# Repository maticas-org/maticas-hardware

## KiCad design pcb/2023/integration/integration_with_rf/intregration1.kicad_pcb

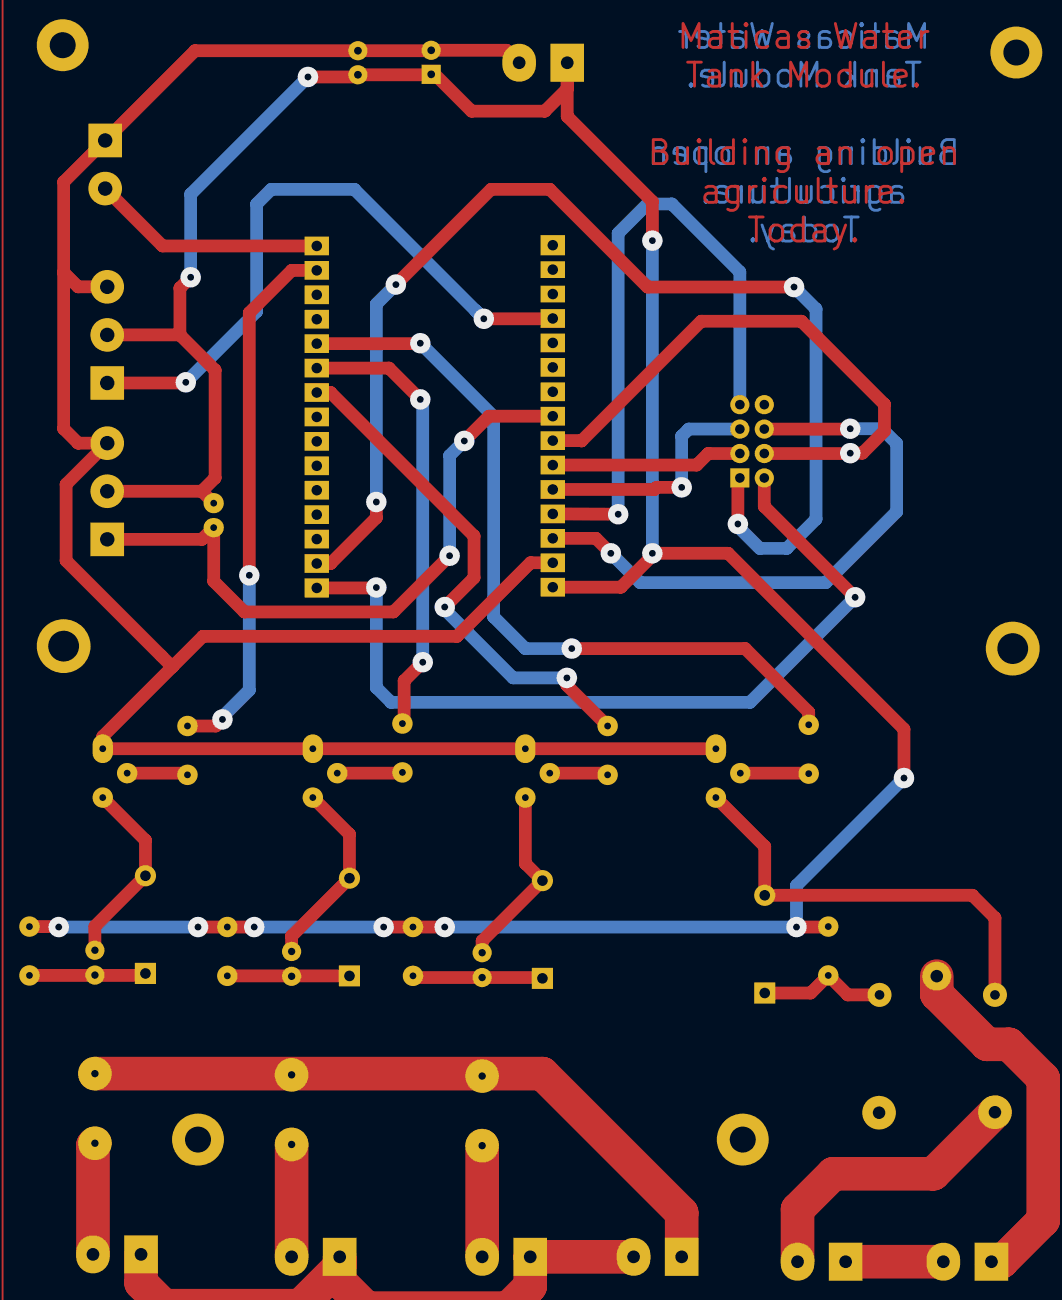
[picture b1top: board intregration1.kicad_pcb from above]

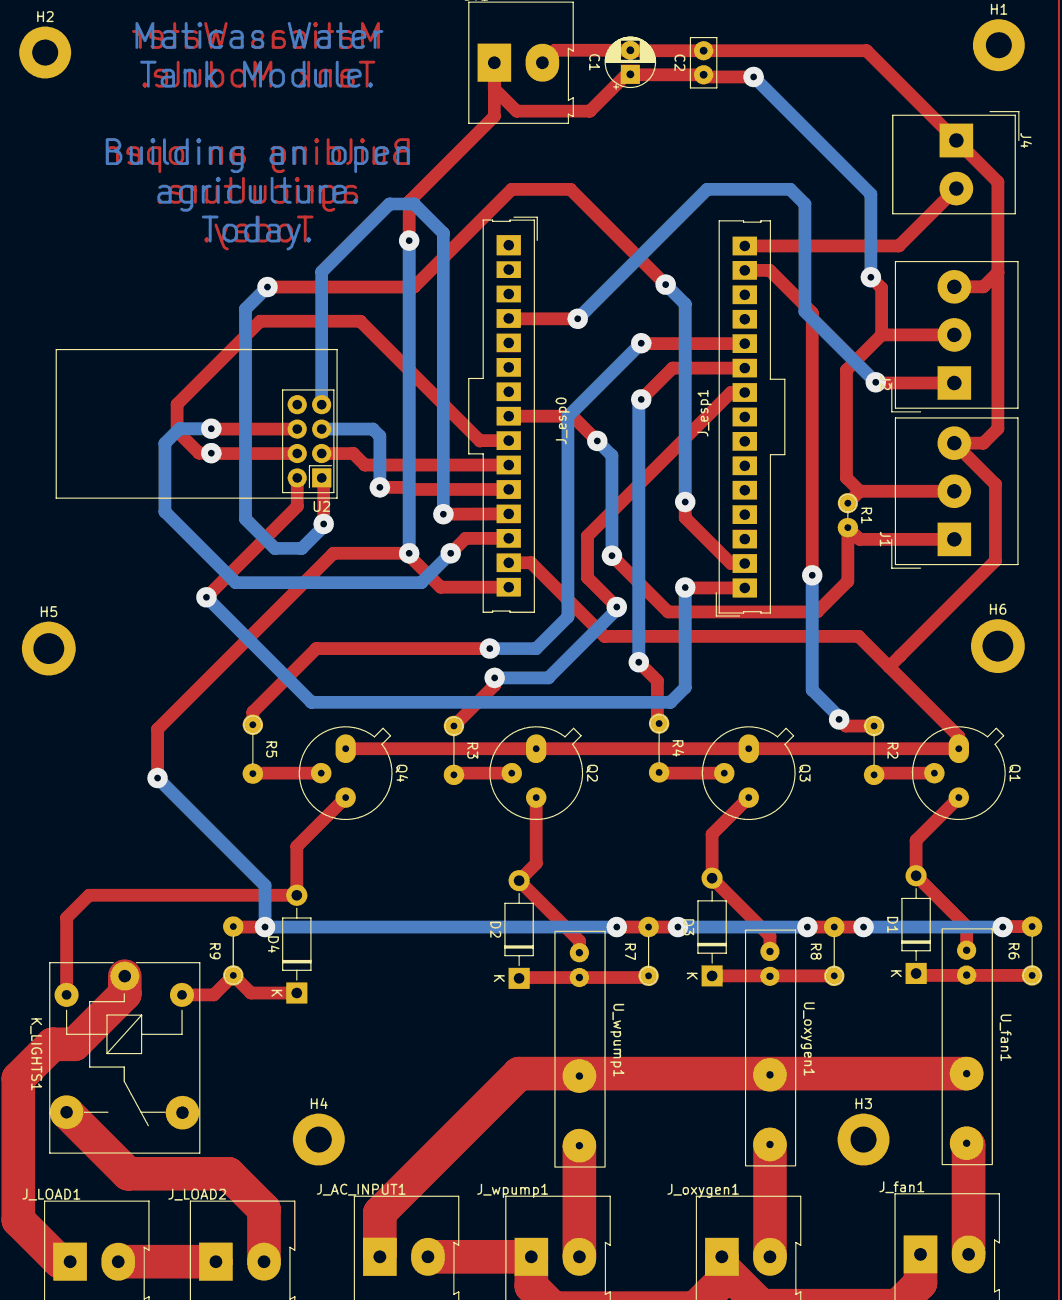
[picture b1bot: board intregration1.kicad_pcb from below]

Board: 2 copper layers, 42 parts (42 on the bottom side), 36 nets.

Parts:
5V1: Screw_Terminal_01x02; TerminalBlock_Altech_AK300-2_P5.00mm
C1: C_Polarized; CP_Radial_D5.0mm_P2.50mm
C2: C_Generic; C_Disc_D5.0mm_W2.5mm_P2.50mm
D1, D2, D3, D4: 1N4004; D_DO-41_SOD81_P10.16mm_Horizontal
H1, H2, H3, H4: MountingHole; MountingHole_2.7mm_M2.5_Pad
H5, H6: MountingHole; MountingHole_3.2mm_M3_DIN965_Pad
J1, J2: Screw_Terminal_01x03; Altech_AK300_1x03_P5.00mm_45-Degree
J4: Screw_Terminal_01x02; Altech_AK300_1x02_P5.00mm_45-Degree
J_AC_INPUT1: Screw_Terminal_01x02; TerminalBlock_Altech_AK300-2_P5.00mm
J_LOAD1, J_LOAD2: Screw_Terminal_01x02; TerminalBlock_Altech_AK300-2_P5.00mm
J_esp0, J_esp1: Conn_01x15_Female; Connector_Molex_Molex_SL_171971-0015_1x15_P2.54mm_Vertical_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
J_fan1: Screw_Terminal_01x02; TerminalBlock_Altech_AK300-2_P5.00mm
J_oxygen1: Screw_Terminal_01x02; TerminalBlock_Altech_AK300-2_P5.00mm
J_wpump1: Screw_Terminal_01x02; TerminalBlock_Altech_AK300-2_P5.00mm
K_LIGHTS1: SANYOU_SRD_Form_C; Relay_SPDT_SANYOU_SRD_Series_Form_C
Q1, Q2, Q3, Q4: 2N2219; TO-39-3
R1: 4.7k; R_Axial_DIN0204_L3.6mm_D1.6mm_P2.54mm_Vertical
R2, R3, R4, R5: 660; R_Axial_DIN0204_L3.6mm_D1.6mm_P5.08mm_Vertical
R6, R7, R8, R9: R; R_Axial_DIN0204_L3.6mm_D1.6mm_P5.08mm_Vertical
U2: NRF24L01_Breakout; nRF24L01_Breakout
U_fan1: 34.81-8240; G3MB-202P
U_oxygen1: 34.81-8240; G3MB-202P
U_wpump1: 34.81-8240; G3MB-202P

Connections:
3V3: J_esp1.1, U2.2 (VCC)
5v: 5V1.1, C1.1, C2.1, J1.2, J2.2, J_esp0.15, R1.1, R6.2, R7.2, R8.2, R9.2
AC1: J_AC_INPUT1.1, U_fan1.11, U_oxygen1.11, U_wpump1.11
AC2: J_AC_INPUT1.2, J_fan1.1, J_oxygen1.1, J_wpump1.1
D12: J_esp0.12, U2.7 (MISO)
D13: J_esp0.13, U2.6 (MOSI)
D14: J_esp0.11, U2.5 (SCK)
D18: J_esp1.9, R3.1
D19: J_esp1.10, R4.1
D21: J_esp1.11, R5.1
D22: J_esp1.14, R2.1
D23: J4.2, J_esp1.15
D25: J1.1, J_esp0.8, R1.2
D26: J_esp0.9, U2.4 (~CSN)
D27: J_esp0.10, U2.3 (CE)
D34: J2.1, J_esp0.4
GND2: J_esp1.2, U2.1 (GND)
GND5V: 5V1.2, C1.2, C2.2, J1.3, J2.3, J4.1, J_esp0.14, Q1.1 (E), Q2.1 (E), Q3.1 (E), Q4.1 (E)
GND LOAD: J_LOAD1.2, J_LOAD2.1
LOAD IN: J_LOAD1.1, K_LIGHTS1.1
unnamed: D1.2 (A), Q1.3 (C), U_fan1.A2
unnamed: D1.1 (K), R6.1, U_fan1.A1
unnamed: D2.2 (A), Q2.3 (C), U_wpump1.A2
unnamed: D2.1 (K), R7.1, U_wpump1.A1
unnamed: D3.2 (A), Q3.3 (C), U_oxygen1.A2
unnamed: D3.1 (K), R8.1, U_oxygen1.A1
unnamed: D4.2 (A), K_LIGHTS1.2, Q4.3 (C)
unnamed: D4.1 (K), K_LIGHTS1.5, R9.1
unnamed: J_fan1.2, U_fan1.14
unnamed: J_oxygen1.2, U_oxygen1.14
unnamed: J_wpump1.2, U_wpump1.14
unnamed: Q1.2 (B), R2.2
unnamed: Q2.2 (B), R3.2
unnamed: Q3.2 (B), R4.2
unnamed: Q4.2 (B), R5.2
Normally O: J_LOAD2.2, K_LIGHTS1.3

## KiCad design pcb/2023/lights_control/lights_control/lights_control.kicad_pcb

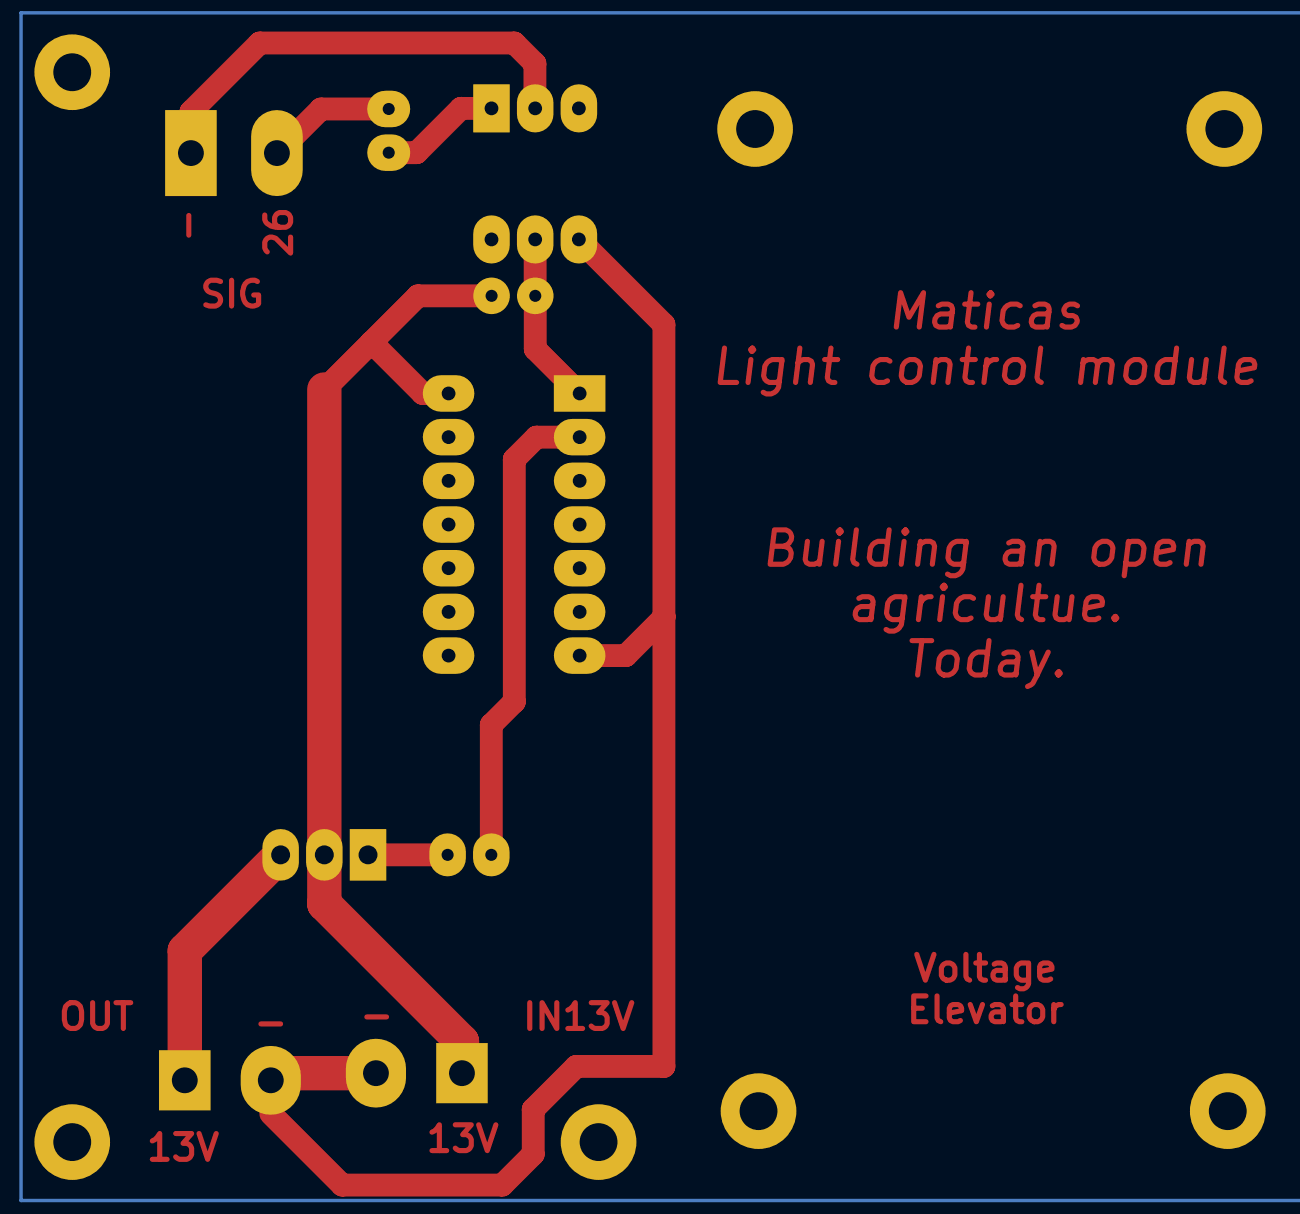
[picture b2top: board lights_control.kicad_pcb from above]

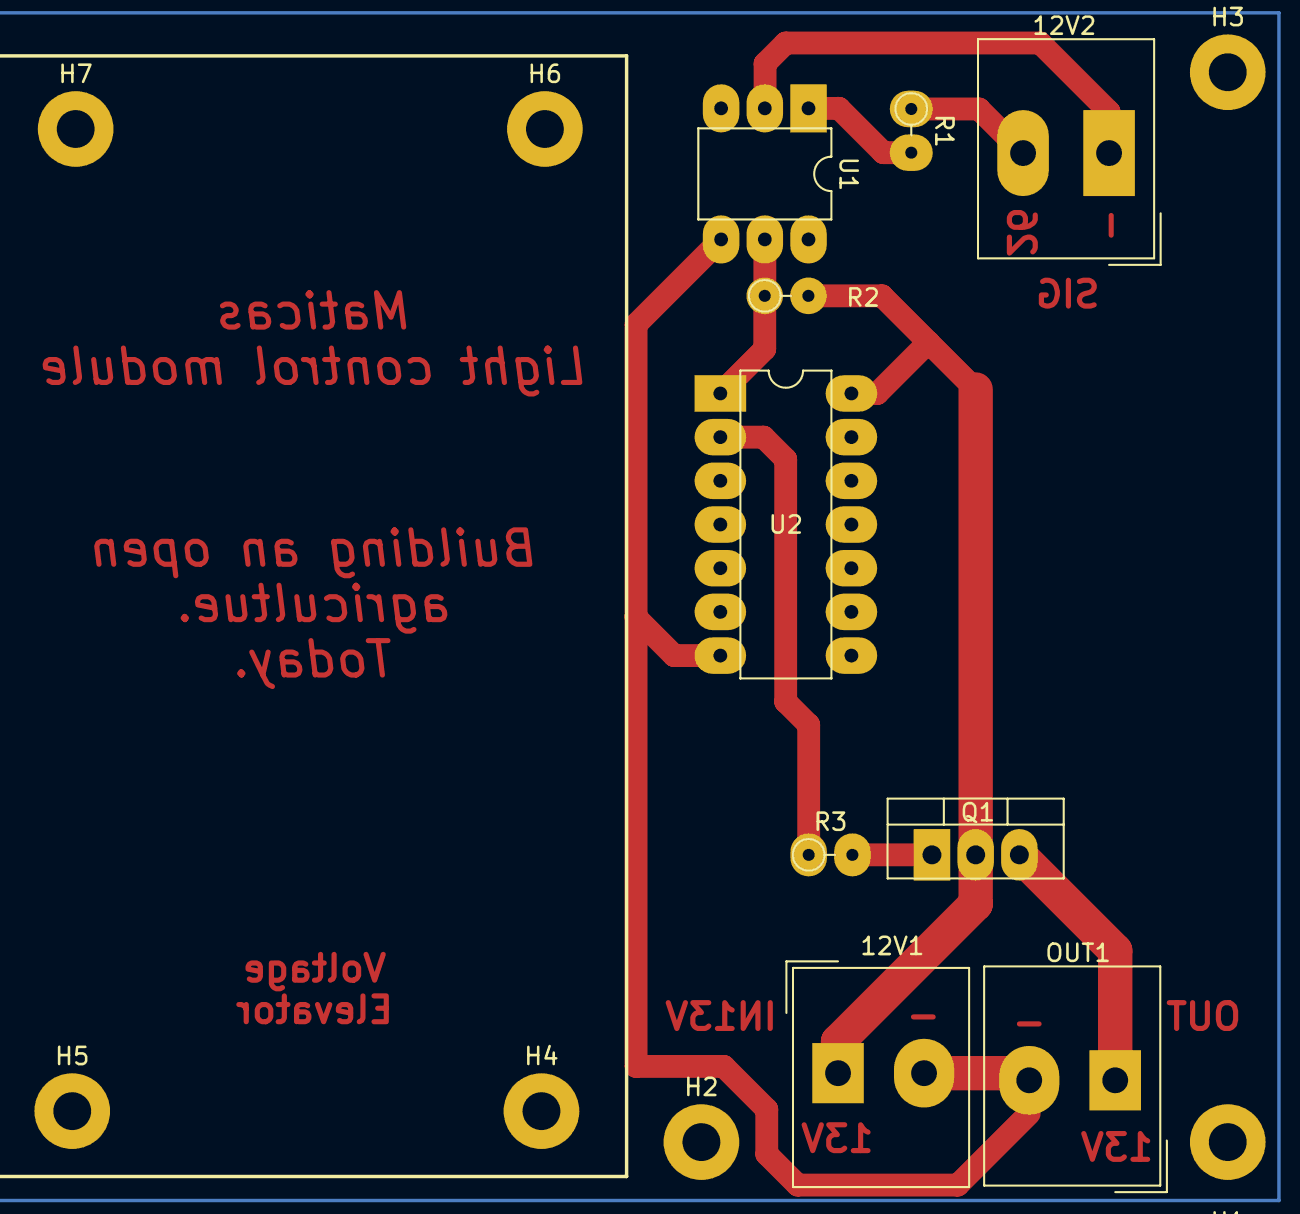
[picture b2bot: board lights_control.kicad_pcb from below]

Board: 2 copper layers, 16 parts (16 on the bottom side), 9 nets.

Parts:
12V1, 12V2: Screw_Terminal_01x02; Altech_AK300_1x02_P5.00mm_45-Degree
H1, H2, H3, H4, H5, H6, H7: MountingHole; MountingHole_2.2mm_M2_Pad
OUT1: Screw_Terminal_01x02; Altech_AK300_1x02_P5.00mm_45-Degree
Q1: TIP122; TO-220-3_Vertical
R1: 100; R_Axial_DIN0204_L3.6mm_D1.6mm_P2.54mm_Vertical
R2: 10k; R_Axial_DIN0204_L3.6mm_D1.6mm_P2.54mm_Vertical
R3: 10; R_Axial_DIN0204_L3.6mm_D1.6mm_P2.54mm_Vertical
U1: 4N25; DIP-6_W7.62mm
U2: 40106; DIP-14_W7.62mm

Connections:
12v: 12V1.1, Q1.2 (C), R2.2, U2.14 (VDD)
D26: 12V2.2, R1.1
GND12V: 12V1.2, OUT1.2, U1.4, U2.7 (VSS)
GND SIG: 12V2.1, U1.2
unnamed: OUT1.1, Q1.3 (E)
unnamed: Q1.1 (B), R3.2
unnamed: R1.2, U1.1
unnamed: R2.1, U1.5, U2.1
unnamed: R3.1, U2.2

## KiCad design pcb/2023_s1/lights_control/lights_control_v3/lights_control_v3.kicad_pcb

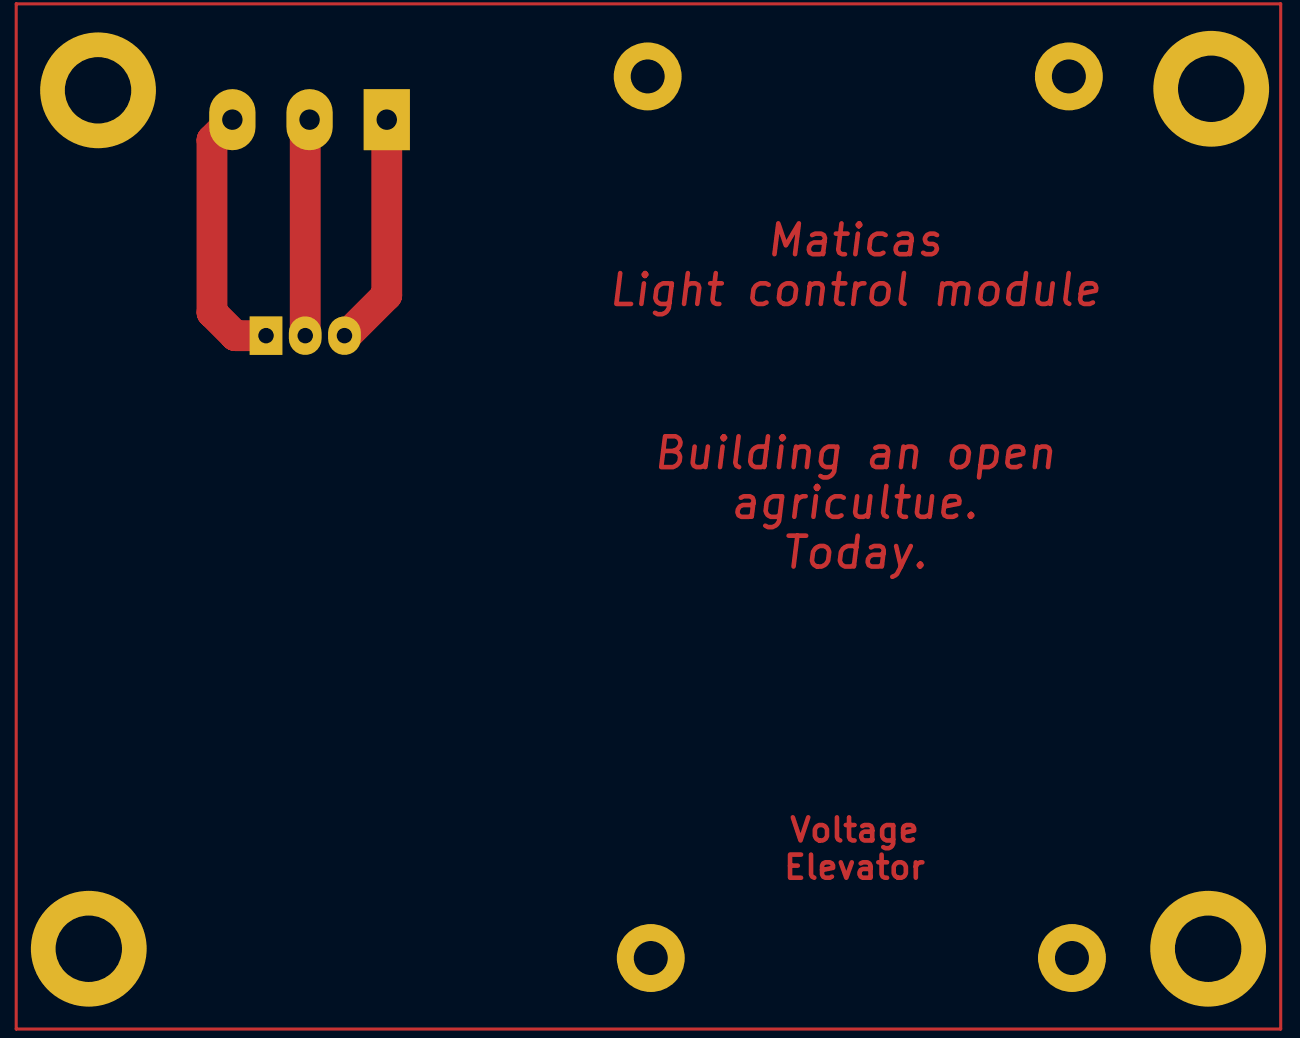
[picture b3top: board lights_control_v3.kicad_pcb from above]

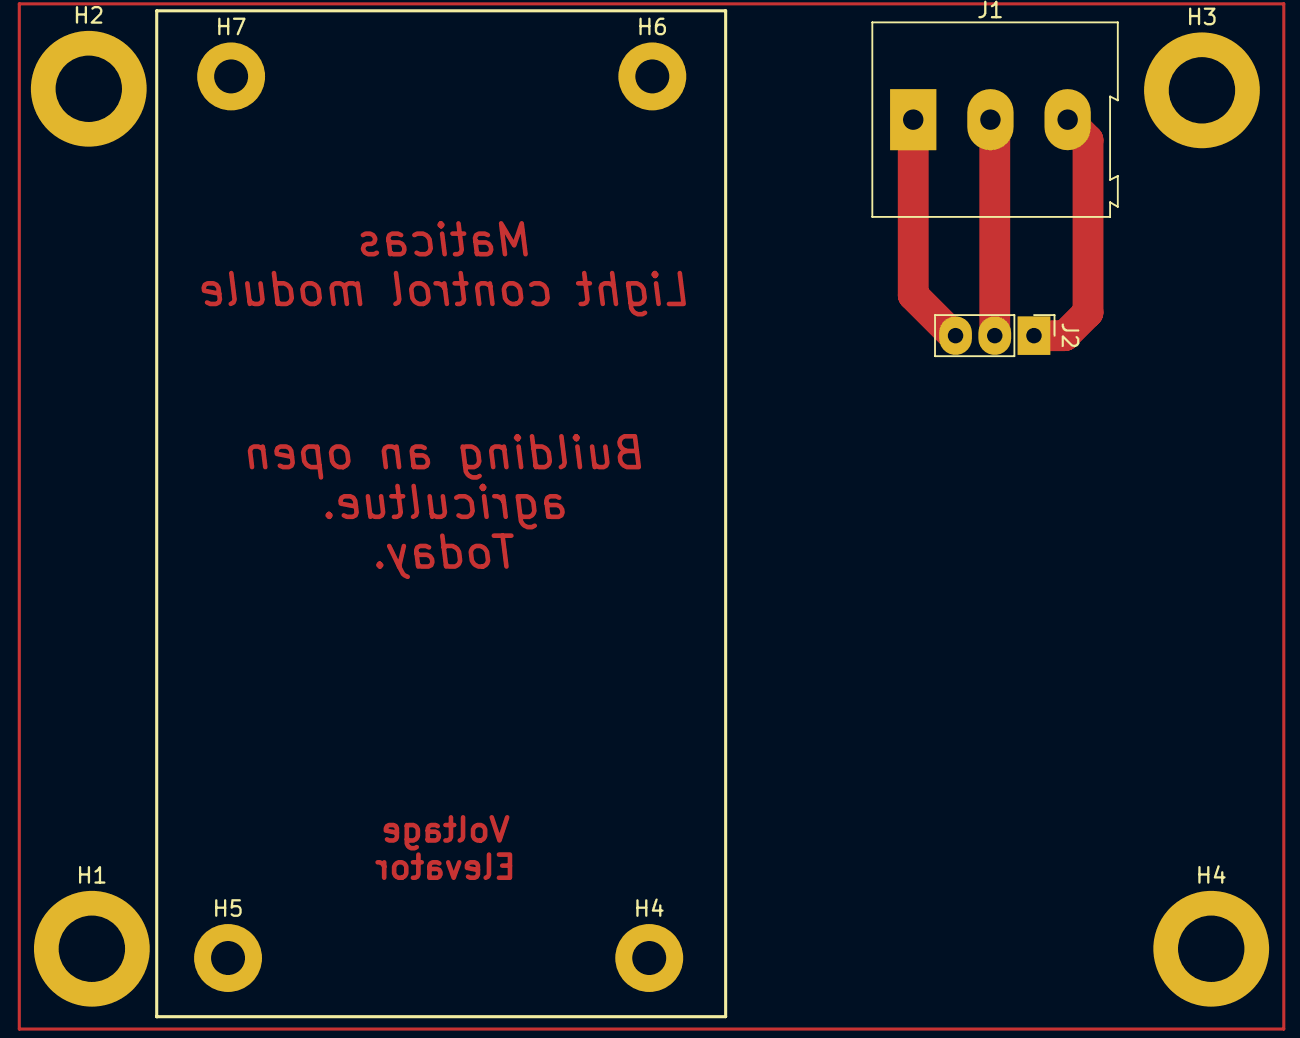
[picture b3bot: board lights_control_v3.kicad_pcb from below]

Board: 2 copper layers, 10 parts (10 on the bottom side), 3 nets.

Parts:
H1, H2, H3, H4: MountingHole; MountingHole_4.3mm_M4_DIN965_Pad
H4#2, H5, H6, H7: MountingHole; MountingHole_2.2mm_M2_Pad
J1: Screw_Terminal_01x03; TerminalBlock_Altech_AK300-3_P5.00mm
J2: Conn_01x03_Male; PinHeader_1x03_P2.54mm_Vertical

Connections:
3.3V SIG: J1.3, J2.1
5V+: J1.2, J2.2
GND5V: J1.1, J2.3

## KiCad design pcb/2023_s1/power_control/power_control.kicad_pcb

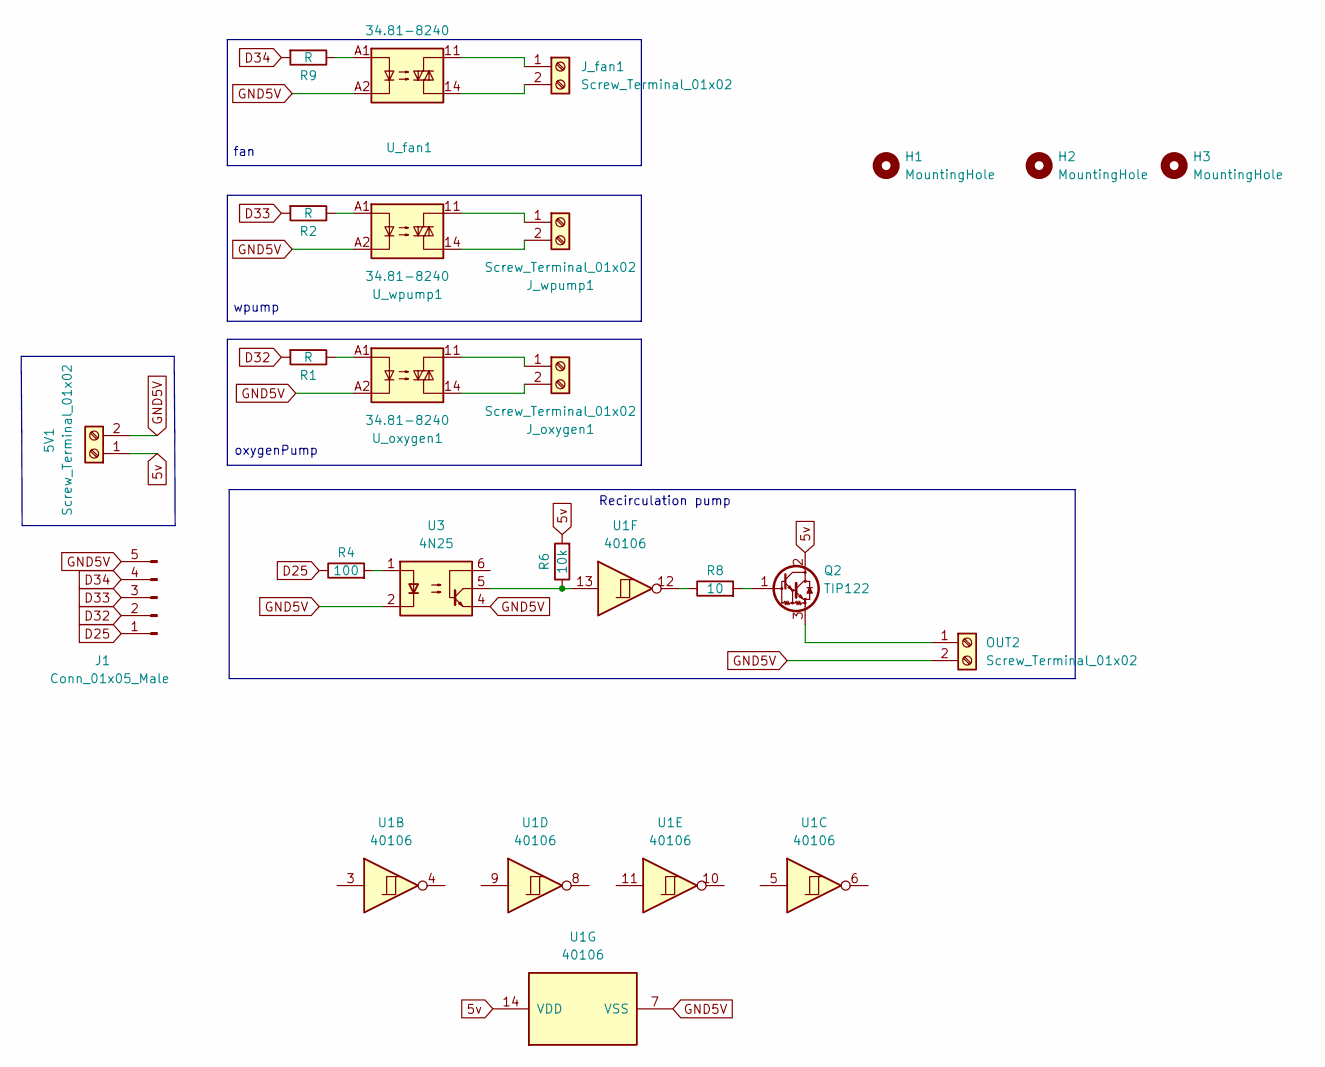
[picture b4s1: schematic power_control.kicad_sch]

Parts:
5V1: Screw_Terminal_01x02; TerminalBlock_Altech_AK300-2_P5.00mm
H1, H2, H3: MountingHole; MountingHole_3.2mm_M3_DIN965_Pad
J1: Conn_01x05_Male; JST_EH_B5B-EH-A_1x05_P2.50mm_Vertical
J_fan1: Screw_Terminal_01x02; TerminalBlock_Altech_AK300-2_P5.00mm
J_oxygen1: Screw_Terminal_01x02; TerminalBlock_Altech_AK300-2_P5.00mm
J_wpump1: Screw_Terminal_01x02; TerminalBlock_Altech_AK300-2_P5.00mm
OUT2: Screw_Terminal_01x02; TerminalBlock_Altech_AK300-2_P5.00mm
Q2: TIP122; TO-220-3_Vertical
R1, R2, R9: R; R_Axial_DIN0204_L3.6mm_D1.6mm_P5.08mm_Vertical
R4: 100; R_Axial_DIN0204_L3.6mm_D1.6mm_P2.54mm_Vertical
R6: 10k; R_Axial_DIN0204_L3.6mm_D1.6mm_P2.54mm_Vertical
R8: 10; R_Axial_DIN0204_L3.6mm_D1.6mm_P2.54mm_Vertical
U1: 40106; DIP-14_W7.62mm
U3: 4N25; DIP-6_W7.62mm
U_fan1: 34.81-8240; Finder_34.81
U_oxygen1: 34.81-8240; Finder_34.81
U_wpump1: 34.81-8240; Finder_34.81

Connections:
5v: 5V1.1, Q2.2 (C), R6.2, U1.14 (VDD)
D25: J1.1, R4.1
D32: J1.2, R1.2
D33: J1.3, R2.2
D34: J1.4, R9.2
GND5V: 5V1.2, J1.5, OUT2.2, U1.7 (VSS), U3.2, U3.4, U_fan1.A2, U_oxygen1.A2, U_wpump1.A2
unnamed: J_fan1.1, U_fan1.11
unnamed: J_fan1.2, U_fan1.14
unnamed: J_oxygen1.1, U_oxygen1.11
unnamed: J_oxygen1.2, U_oxygen1.14
unnamed: J_wpump1.1, U_wpump1.11
unnamed: J_wpump1.2, U_wpump1.14
unnamed: OUT2.1, Q2.3 (E)
unnamed: Q2.1 (B), R8.2
unnamed: R1.1, U_oxygen1.A1
unnamed: R2.1, U_wpump1.A1
unnamed: R4.2, U3.1
unnamed: R6.1, U1.13, U3.5
unnamed: R8.1, U1.12
unnamed: R9.1, U_fan1.A1

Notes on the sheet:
fan
wpump
oxygenPump
Recirculation pump

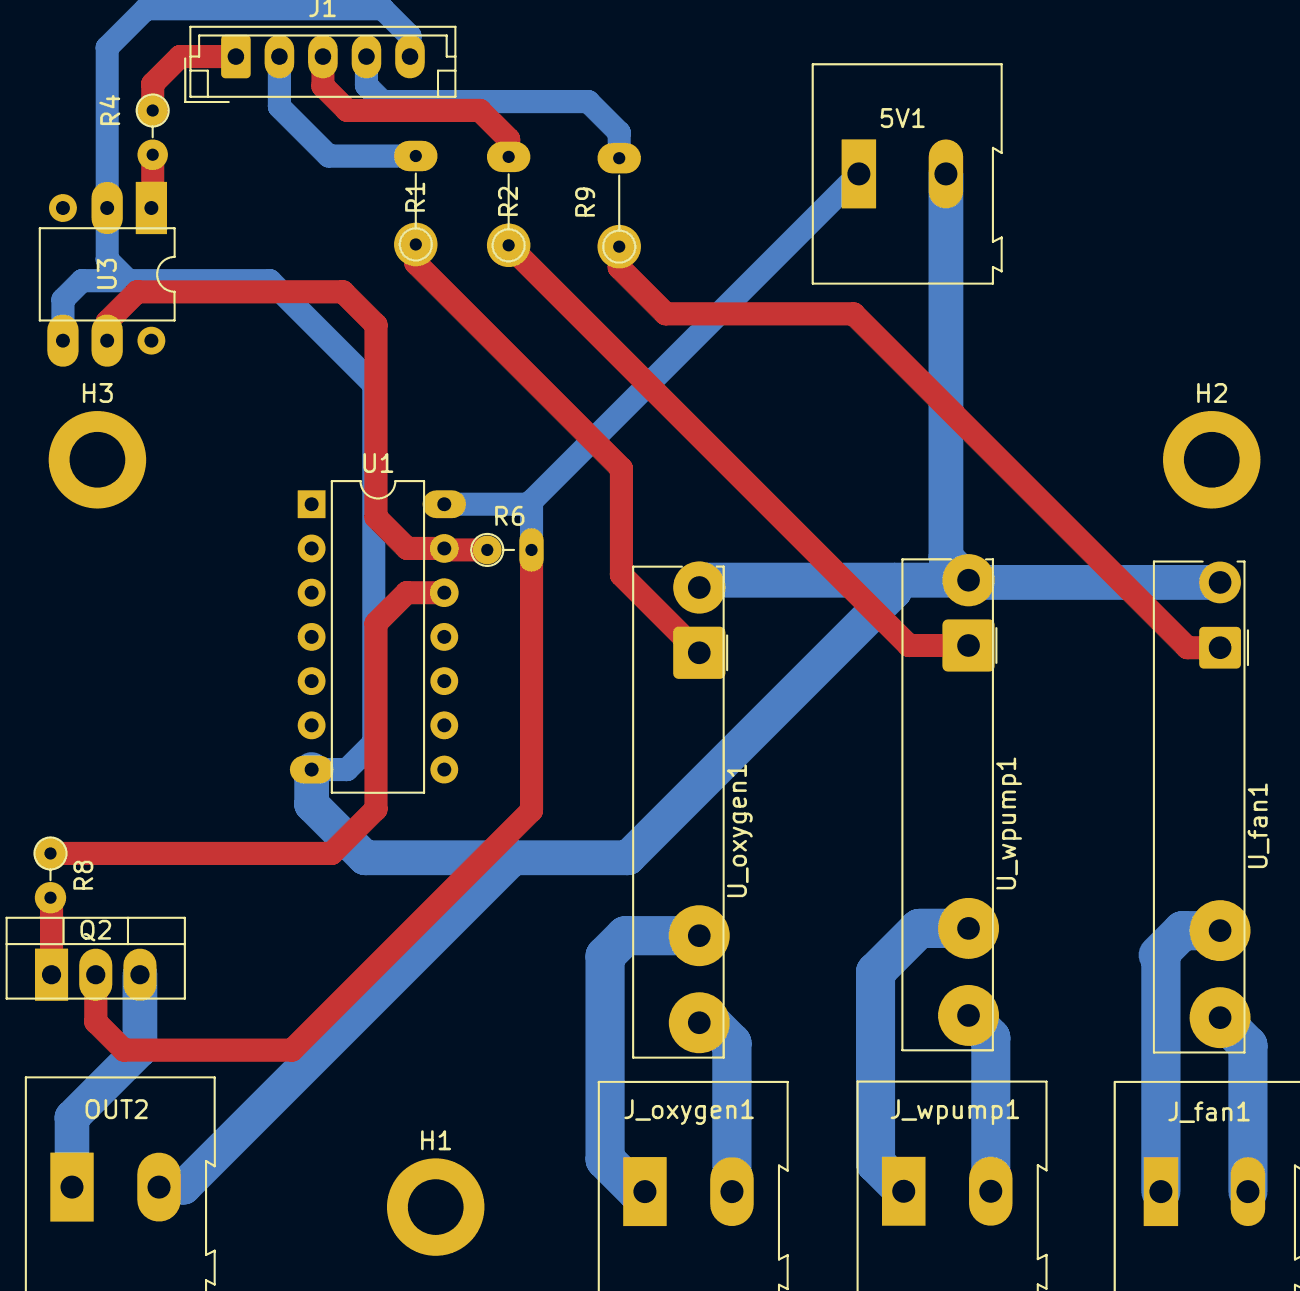
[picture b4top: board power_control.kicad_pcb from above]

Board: 2 copper layers, 21 parts (0 on the bottom side), 20 nets.

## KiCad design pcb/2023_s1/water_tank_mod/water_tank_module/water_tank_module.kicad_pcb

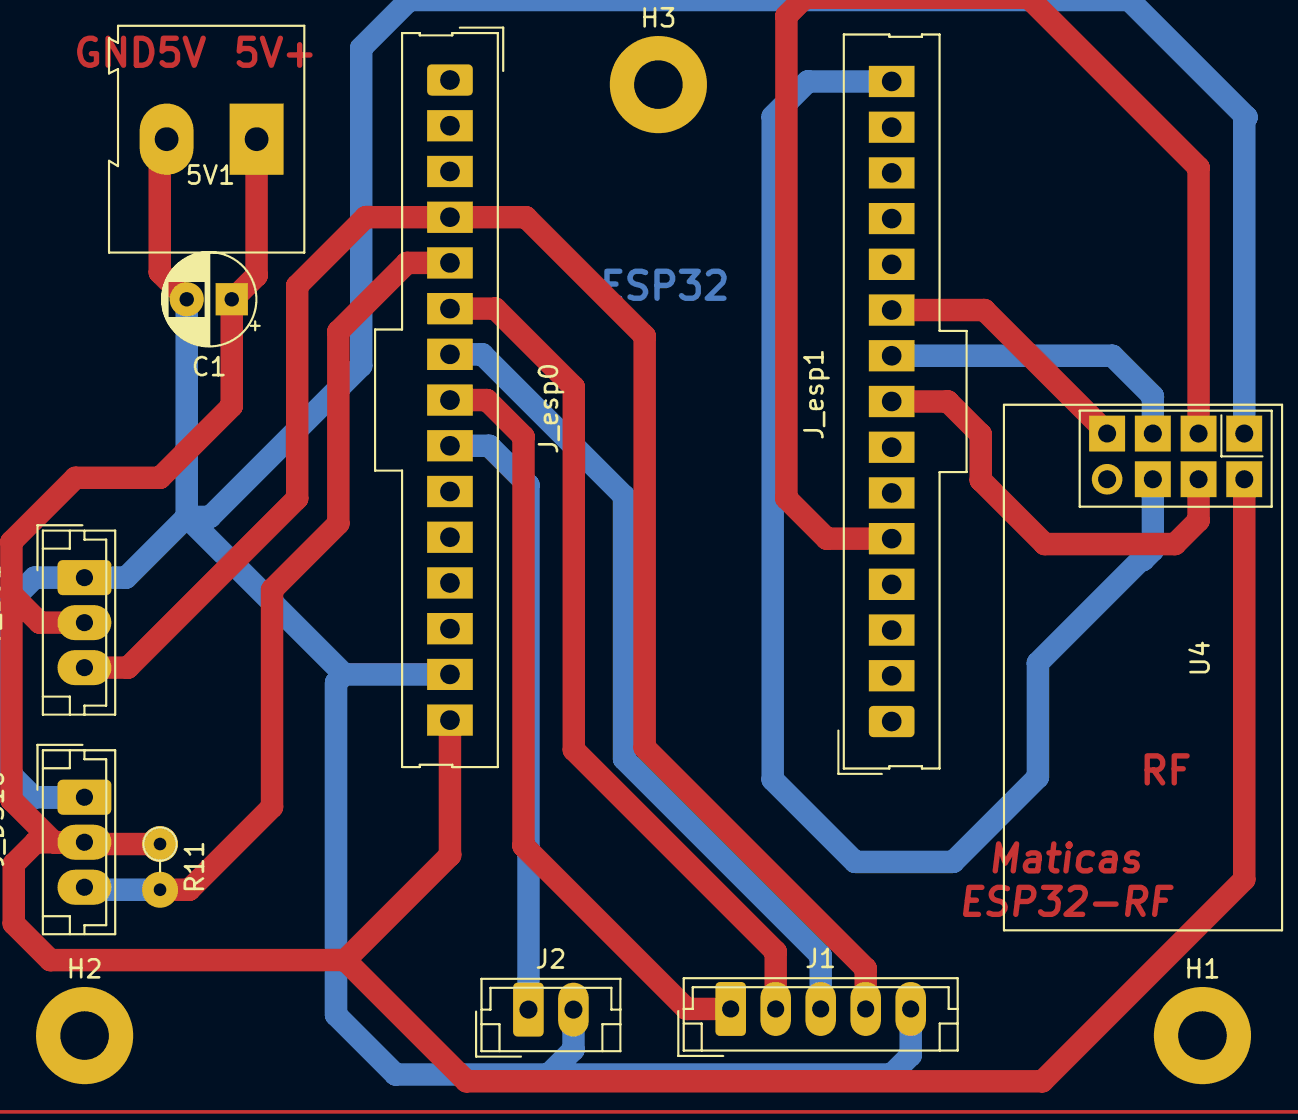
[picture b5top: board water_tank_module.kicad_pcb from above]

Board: 2 copper layers, 13 parts (0 on the bottom side), 13 nets.

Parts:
5V1: Screw_Terminal_01x02; TerminalBlock_Altech_AK300-2_P5.00mm
C1: C_Polarized; CP_Radial_D5.0mm_P2.50mm
H1, H2, H3: MountingHole; MountingHole_2.7mm_M2.5_Pad
J1: Conn_01x05_Male; JST_EH_B5B-EH-A_1x05_P2.50mm_Vertical
J2: Conn_01x02_Male; JST_EH_B2B-EH-A_1x02_P2.50mm_Vertical
J_DS18: Conn_01x03_Male; JST_EH_B3B-EH-A_1x03_P2.50mm_Vertical
J_EC1: Conn_01x03_Male; JST_EH_B3B-EH-A_1x03_P2.50mm_Vertical
J_esp0, J_esp1: Conn_01x15_Female; Connector_Molex_Molex_SL_171971-0015_1x15_P2.54mm_Vertical_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
R11: 4.7k; R_Axial_DIN0204_L3.6mm_D1.6mm_P2.54mm_Vertical
U4: NRF24L01_Breakout; nRF24L01_Breakout

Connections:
5v: 5V1.1, C1.1, J_DS18.2, J_EC1.2, J_esp0.15, R11.1, U4.2 (VCC)
D4: J_esp1.5, U4.3 (CE)
D5: J_esp1.8, U4.4 (~CSN)
D18: J_esp1.9, U4.5 (SCK)
D19: J_esp1.10, U4.7 (MISO)
D23: J_esp1.15, U4.6 (MOSI)
D25: J1.1, J_esp0.8
D26: J2.1, J_esp0.9
D32: J1.2, J_esp0.6
D33: J1.3, J_esp0.7
D34: J1.4, J_EC1.3, J_esp0.4
D35: J_DS18.3, J_esp0.5, R11.2
GND5V: 5V1.2, C1.2, J1.5, J2.2, J_DS18.1, J_EC1.1, J_esp0.14, U4.1 (GND)

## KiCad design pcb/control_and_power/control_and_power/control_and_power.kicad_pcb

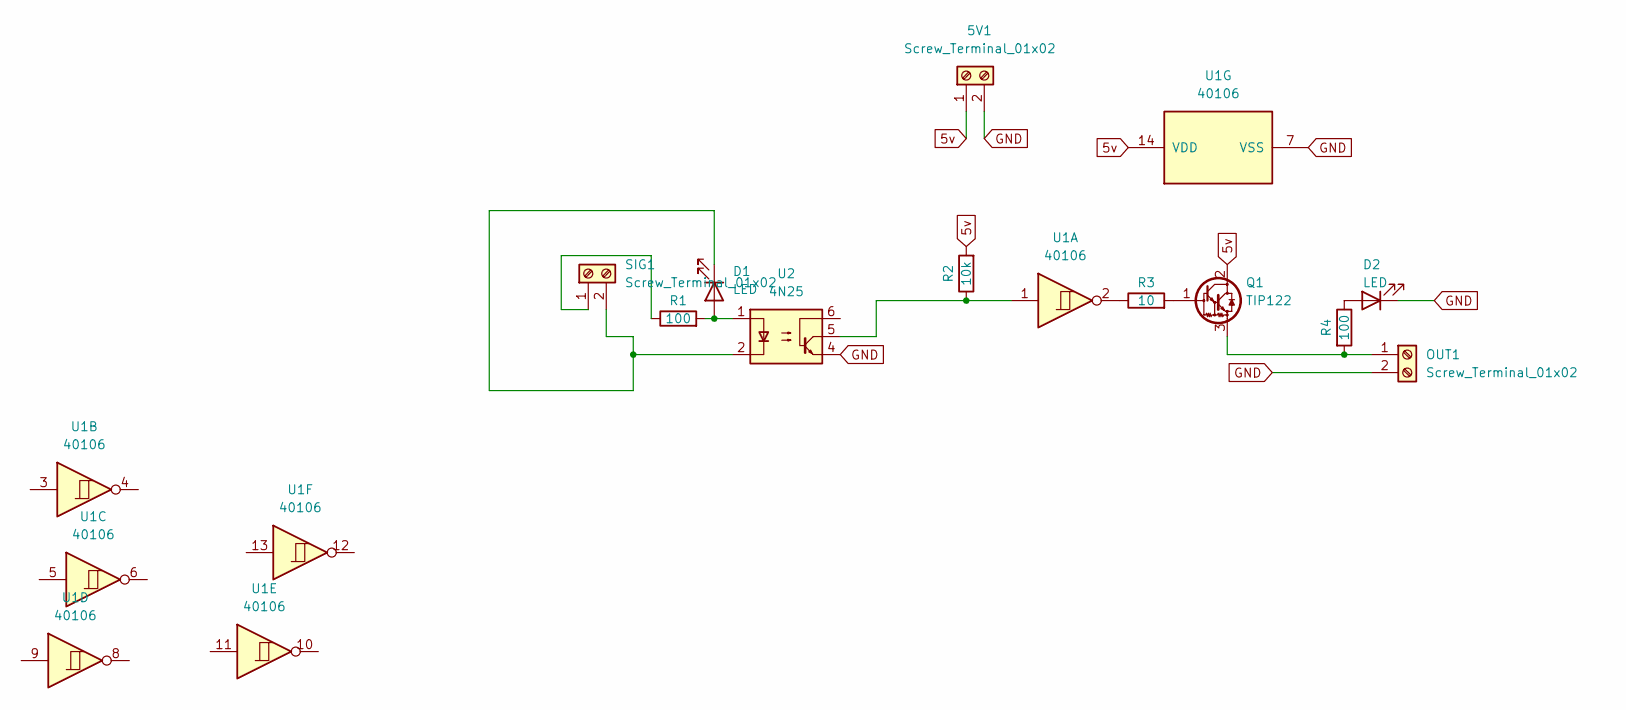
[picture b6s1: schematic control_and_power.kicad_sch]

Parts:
5V1: Screw_Terminal_01x02; TerminalBlock_Altech_AK300-2_P5.00mm
D1, D2: LED; LED_D3.0mm_Clear
OUT1: Screw_Terminal_01x02; TerminalBlock_Altech_AK300-2_P5.00mm
Q1: TIP122; TO-220-3_Vertical
R1, R4: 100; R_Axial_DIN0204_L3.6mm_D1.6mm_P2.54mm_Vertical
R2: 10k; R_Axial_DIN0204_L3.6mm_D1.6mm_P2.54mm_Vertical
R3: 10; R_Axial_DIN0204_L3.6mm_D1.6mm_P2.54mm_Vertical
SIG1: Screw_Terminal_01x02; TerminalBlock_Altech_AK300-2_P5.00mm
U1: 40106; DIP-14_W7.62mm
U2: 4N25; DIP-6_W7.62mm

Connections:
5v: 5V1.1, Q1.2 (C), R2.2, U1.14 (VDD)
GND: 5V1.2, D2.1 (K), OUT1.2, U1.7 (VSS), U2.4
unnamed: D1.1 (K), SIG1.2, U2.2
unnamed: D1.2 (A), R1.2, U2.1
unnamed: D2.2 (A), R4.1
unnamed: OUT1.1, Q1.3 (E), R4.2
unnamed: Q1.1 (B), R3.2
unnamed: R2.1, U1.1, U2.5
unnamed: R3.1, U1.2
unnamed: R1.1, SIG1.1

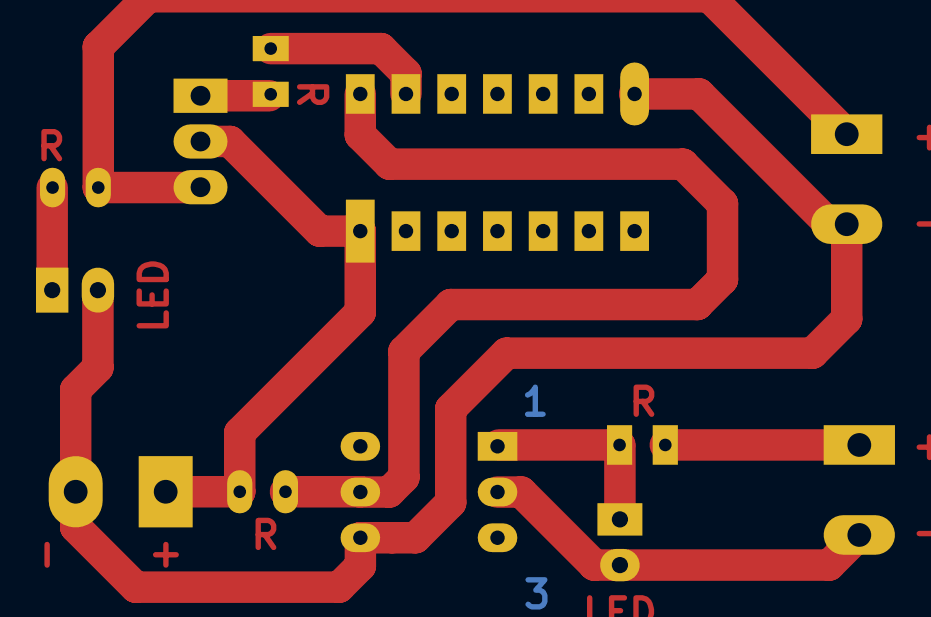
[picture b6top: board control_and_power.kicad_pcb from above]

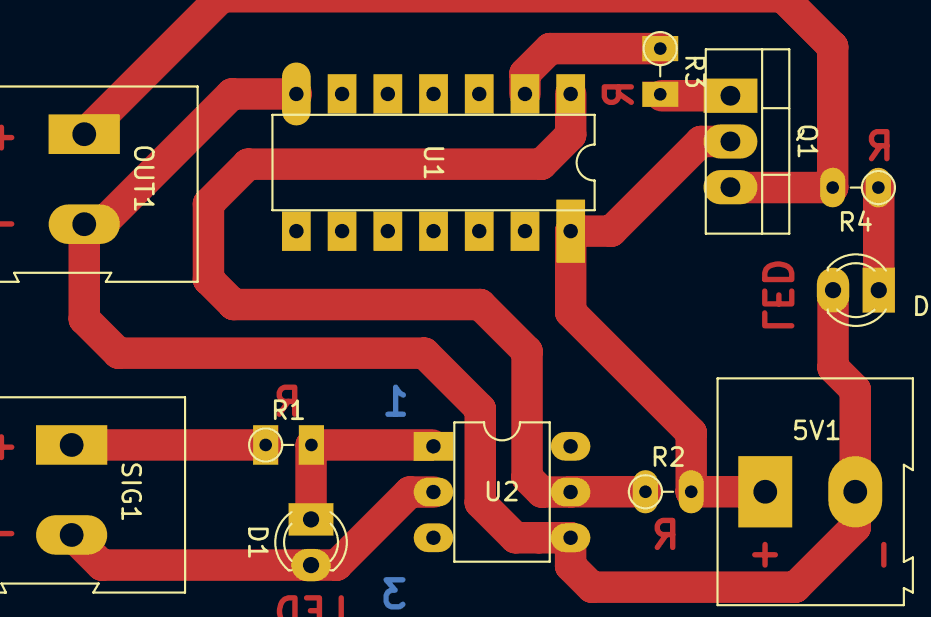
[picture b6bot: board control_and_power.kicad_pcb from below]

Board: 2 copper layers, 12 parts (12 on the bottom side), 10 nets.
